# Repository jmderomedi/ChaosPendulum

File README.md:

# ChaosPendulum
Physics capstone project: Creating and analyzing chaotic motion  
This project involved the creation and analytics of chaotic motion

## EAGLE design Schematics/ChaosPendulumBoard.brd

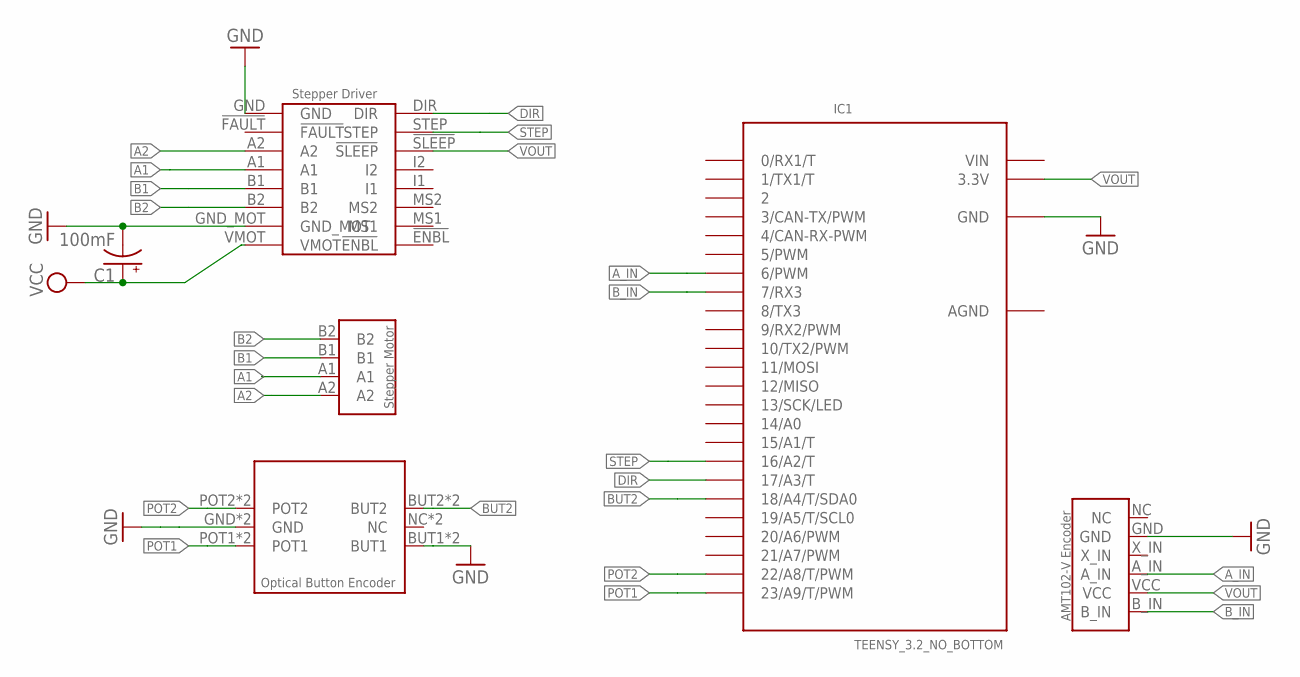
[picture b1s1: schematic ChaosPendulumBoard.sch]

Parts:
C1: 100mF; CPOL-RADIAL-100UF-25V
IC1: TEENSY_3.2_NO_BOTTOM
U$2: STEPPER_MOTOR_MP6500
U$3: OPTICAL_ENCODER_AMT102-V
U$4: STEPPER_NEMA_14
U$5: OPTICAL_BUTTON_ENCODER

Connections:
A1: U$2.A1, U$4.A1
A2: U$2.A2, U$4.A2
AGND: IC1.AGND
A_IN: IC1.6 (6/PWM), U$3.A_IN
B1: U$2.B1, U$4.B1
B2: U$2.B2, U$4.B2
BUT2: IC1.18/A4 (18/A4/T/SDA0), U$5.BUT2, U$5.BUT2_EXT (BUT2)
B_IN: IC1.7 (7/RX3), U$3.B_IN
DIR: IC1.17/A3 (17/A3/T), U$2.DIR
GND: C1.2 (-), IC1.GND, U$2.GND, U$2.GND_MOT, U$3.GND, U$5.BUT1, U$5.BUT1_EXT (BUT1), U$5.GND, U$5.GND_EXT (GND)
POT1: IC1.23/A9 (23/A9/T/PWM), U$5.POT1, U$5.POT1_EXT (POT1)
POT2: IC1.22/A8 (22/A8/T/PWM), U$5.POT2, U$5.POT2_EXT (POT2)
STEP: IC1.16/A2 (16/A2/T), U$2.STEP
VCC: C1.1 (+), U$2.VMOT
VIN: IC1.VIN
VOUT: IC1.3.3V, U$2.!SLEEP, U$3.VCC

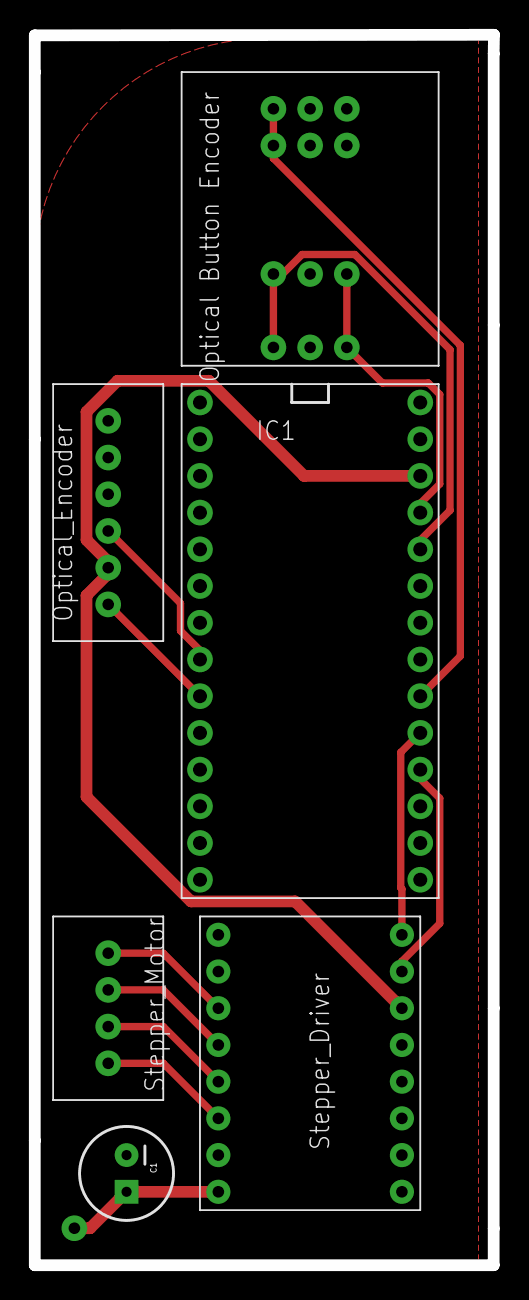
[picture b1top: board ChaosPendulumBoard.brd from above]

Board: 2 copper layers, 31.8 x 85.1 mm, 6 parts (0 on the bottom side), 14 nets.

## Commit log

2018-09-26 Moved over from Bitbucket
2018-09-26 Blocked out test code
2018-10-02 Moved SavLayFilter to its own repo; Completed LCD display
2018-10-02 Fixed LCD screen and added Motor Omega
2018-10-02 Added Flywheel encoder code as a function
2018-10-02 Created README.md
    Only a placeholder for now
2018-10-02 testing code
2018-10-02 Cleaned up flywheel code and added streaming code
2018-10-03 Changed pins to match new hardware design
2018-10-09 Fixed resolution error and data streaming
2018-10-09 Added first data plot
2018-10-17 This is a test commit
2018-10-17 test 2
2018-10-31 Started restart motor function for manual control
2018-11-05 Keeping to work on adding manual functionality
2018-11-06 Branch to work on new motor library
2018-11-06 Changed functions to accept new library
2018-11-13 Tuned the button encoder and started with flywheel resolution
2018-11-13 Reworked flywheel resolution and fixed digitized data issue
2018-11-13 Added test results
2018-11-14 Moved around data collection loop
2018-11-15 Reworked test files for better understanding
2018-11-15 Adding counter to keep track of each PoinCare Section
2018-11-27 Added motor angle printout
2018-11-27 Changed into motor position control loop
2018-11-27 Tweaked the speeds and added arrays to save data
2018-11-27 Added SavLayFilter methods
2018-11-27 Removed some white space
2018-11-29 changed when the data is taken
2018-11-29 added testing function to group print lines
2018-11-29 Added testing()
2018-11-30 Fixed white space and comments
2018-11-30 Using the libraries new pointer system
2018-12-03 Changed printing function around
2018-12-11 Modified comments and deleted old pointless code
2018-12-11 Added excel sheets of current analysis
2018-12-13 Added compiled data and analysis
2018-12-20 Added schematics for the pendulum; Still needs work
2019-01-23 Added test to find frequencies of the system
2019-01-28 Rearranged board for better optimization
2019-01-28 Almost complete optimation
2019-01-28 Finished optimization

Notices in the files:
parts and their libraries:
SparkFun-Capacitors: Licensing: Creative Commons ShareAlike 4.0 International - https://creativecommons.org/licenses/by-sa/4.0
